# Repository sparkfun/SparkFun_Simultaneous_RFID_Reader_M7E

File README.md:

SparkFun Simultaneous RFID Reader - M7E Hecto
============================================

[

[*SparkFun Simultaneous RFID Reader - M7E Hecto*](https://www.sparkfun.com/products/24738)

The SparkFun Simultaneous RFID Reader - M7E Hecto features M7E-HECTO UHF RFID reader from JADAK<sup>&copy;</sup>. We loved the capabilities of the previous version of this RFID reader, the M6E, so we created this design featuring the M7E with an on-board USB-C connector and CH340C USB to UART converter to quickly connect the board to a computer and read tags with no soldering required.

Along with the USB-C connector, the Simultaneous RFID Reader 3.3V has a 0.1"-spaced PTH header for connecting it to an external converter or to a 3.3V microcontroller of your choice to use it with the SparkFun Simultaneous RFID Tag Reader Library. A 2-way switch on the board allows for easy switching between the included communication interfaces.

Repository Contents
-------------------

* **/Documents** - Datasheets, additional product information 
* **/Hardware** - Eagle design files (.brd, .sch)
* **/Production** - Production panel files (.brd)
* **/docs** - Documentation files for the SparkFun Simultaneous RFID Reader - M7E Hecto

Documentation
--------------
* **[Hookup Guide](https://sparkfun.github.io/SparkFun_Simultaneous_RFID_Reader_M7E)** - Basic hookup guide for the SparkFun Simultaneous RFID Reader - M7E Hecto.
* **[SparkFun Simultaneous RFID Tag Reader Library](https://github.com/sparkfun/SparkFun_Simultaneous_RFID_Tag_Reader_Library)** - Arduino library for SparkFun Simultaneous RFID Readers.

Product Versions
----------------
* [WRL-24738](https://www.sparkfun.com/products/24738) - Initial release

License Information
-------------------

This product is _**open source**_! 

Please review the LICENSE.md file for license information. 

If you have any questions or concerns on licensing, please contact technical support on our [SparkFun forums](https://forum.sparkfun.com/viewforum.php?f=152).

Distributed as-is; no warranty is given.

- Your friends at SparkFun.

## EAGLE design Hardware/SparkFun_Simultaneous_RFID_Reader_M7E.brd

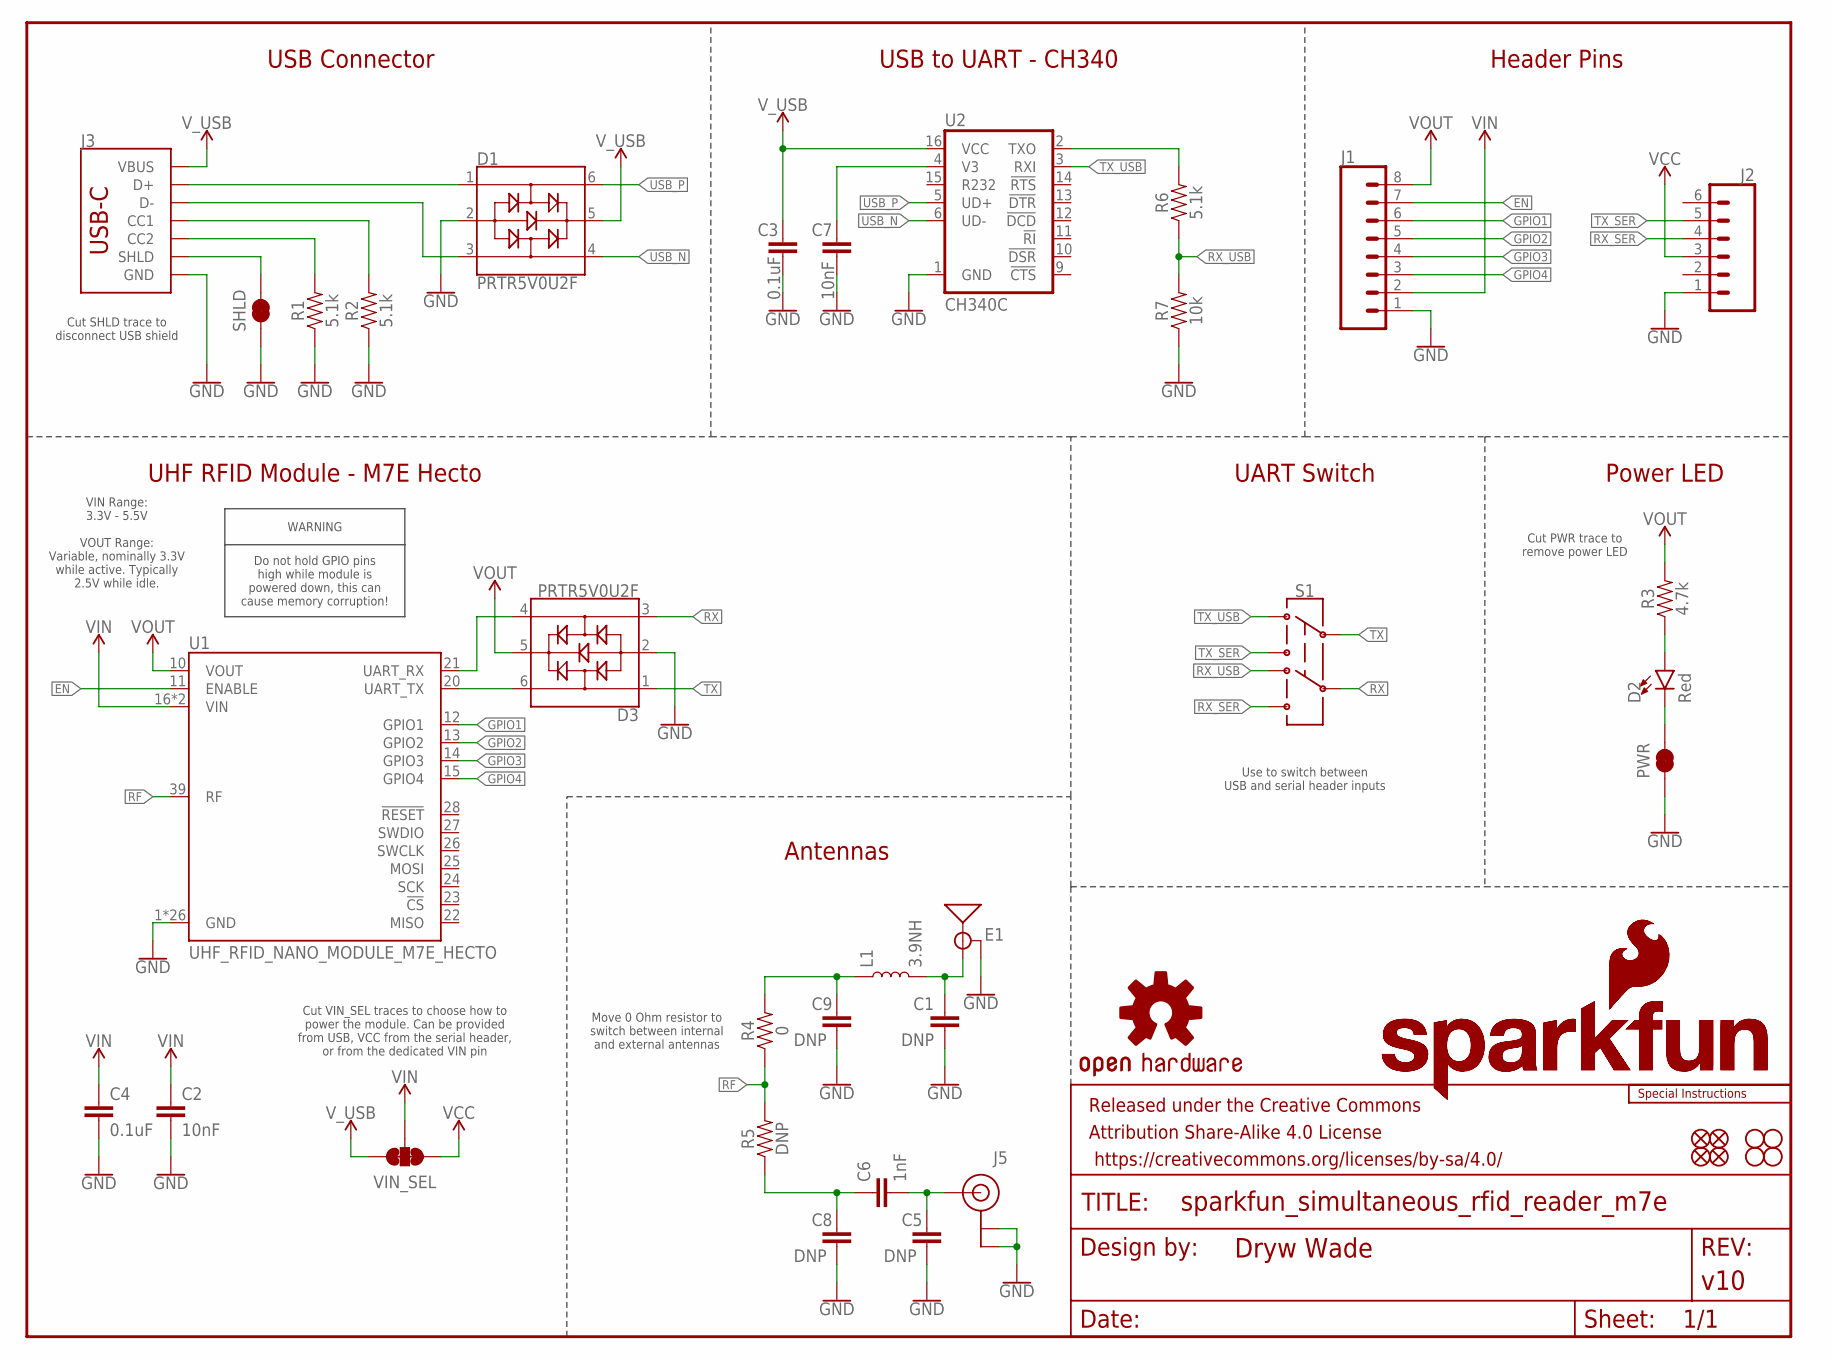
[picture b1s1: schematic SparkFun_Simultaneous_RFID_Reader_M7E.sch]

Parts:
C1, C5, C8, C9: DNP; 0603
C2, C7: 10nF; 0603
C3, C4: 0.1uF; 0603
C6: 1nF; 0603
D1, D3: PRTR5V0U2F; SOT886
D2: Red; LED-0603
E1: ANTENNA-GROUNDEDTRACE-915MHZ; TRACE_ANTENNA_915MHZ_THINGMAGIC
FD1, FD2, FD3, FD4: FIDUCIAL1X2; FIDUCIAL-1X2
FRAME1: FRAME-LETTER; CREATIVE_COMMONS
H1, H2, H3, H4: STAND-OFF
J1: CONN_08NO_SILK_DNP; 1X08_NO_SILK
J2: CONN_06NO_SILK_NO_POP; 1X06_NO_SILK
J3: USB_C_2-LAYER_PADS; USB-C-16P-2LAYER-PADS
J5: U.FL
L1: 3.9NH; 0603
LOGO1: OSHW-LOGOM; OSHW-LOGO-M
LOGO2, LOGO3: SFE_LOGO_NAME_FLAME.2_INCH; SFE_LOGO_NAME_FLAME_.2
LOGO4: SPECIAL_INSTRUCTIONS-ORDERING; ORDERING_INSTRUCTIONS
PWR: JUMPER-SMT_2_NC_TRACE_SILK; SMT-JUMPER_2_NC_TRACE_SILK
R1, R2, R6: 5.1k; 0603
R3: 4.7k; 0603
R4: 0; 0603
R5: DNP; 0603
R7: 10k; 0603
S1: SWITCH-DPDT-SMD-AYZ0202; SWITCH_DPDT_SMD_AYZ0202
SHLD: JUMPER-SMT_2_NC_TRACE_SILK; SMT-JUMPER_2_NC_TRACE_SILK
U1: UHF_RFID_NANO_MODULE_M7E_HECTO; M7E_HECTO_MODULE
U2: CH340C; SO016
VIN_SEL: JUMPER-SMT_3_2-NC_TRACE_SILK; SMT-JUMPER_3_2-NC_TRACE_SILK

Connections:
EN: J1.7, U1.11 (ENABLE)
GND: C1.2, C2.2, C3.2, C4.2, C5.2, C7.2, C8.2, C9.2, D1.2, D3.2, E1.GND@1 (GND), E1.GND@2 (GND), E1.GND@3 (GND), J1.1, J2.1, J3.GND, J3.GND2 (GND), J5.1 (GND), J5.2 (GND), PWR.1, R1.1, R2.1, R7.1, SHLD.1, U1.1 (GND), U1.2 (GND), U1.3 (GND), U1.4 (GND), U1.5 (GND), U1.6 (GND), U1.7 (GND), U1.8 (GND), U1.9 (GND), U1.18 (GND), U1.19 (GND), U1.29 (GND), U1.30 (GND), U1.31 (GND), U1.32 (GND), U1.33 (GND), U1.34 (GND), U1.35 (GND), U1.36 (GND), U1.37 (GND), U1.38 (GND), U1.40 (GND), U1.41 (GND), U1.GND_PAD1 (GND), U1.GND_PAD2 (GND), U1.GND_PAD3 (GND), U2.1 (GND)
GPIO1: J1.6, U1.12 (GPIO1)
GPIO2: J1.5, U1.13 (GPIO2)
GPIO3: J1.4, U1.14 (GPIO3)
GPIO4: J1.3, U1.15 (GPIO4)
unnamed: C1.1, E1.ANT (SIGNAL), L1.2
unnamed: D2.A, R3.1
unnamed: J3.B5 (CC2), R1.2
unnamed: J3.A5 (CC1), R2.2
unnamed: D1.1, J3.A6 (D+), J3.B6 (D+)
unnamed: D2.C, PWR.2
unnamed: D1.3, J3.A7 (D-), J3.B7 (D-)
unnamed: C6.1, C8.1, R5.1
unnamed: C5.1, C6.2, J5.FEED (SIGNAL)
unnamed: C9.1, L1.1, R4.2
unnamed: C7.1, U2.4 (V3)
unnamed: D3.6, U1.20 (UART_TX)
unnamed: D3.4, U1.21 (UART_RX)
unnamed: R6.2, U2.2 (TXO)
RF: R4.1, R5.2, U1.39 (RF)
RX: D3.3, S1.5
RX_SER: J2.4, S1.4
RX_USB: R6.1, R7.2, S1.6
SHLD: J3.SHLD1 (SHLD), J3.SHLD2 (SHLD), J3.SHLD3 (SHLD), J3.SHLD4 (SHLD), SHLD.2
TX: D3.1, S1.2
TX_SER: J2.5, S1.1
TX_USB: S1.3, U2.3 (RXI)
USB_N: D1.4, U2.6 (UD-)
USB_P: D1.6, U2.5 (UD+)
VCC: J2.3, VIN_SEL.1
VIN: C2.1, C4.1, J1.2, U1.16 (VIN), U1.17 (VIN), VIN_SEL.2
VOUT: D3.5, J1.8, R3.2, U1.10 (VOUT)
V_USB: C3.1, D1.5, J3.VBUS1 (VBUS), J3.VBUS2 (VBUS), U2.16 (VCC), VIN_SEL.3

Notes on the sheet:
WARNING
Do not hold GPIO pins high while module is powered down, this can cause memory corruption!
Cut VIN_SEL traces to choose how to power the module. Can be provided from USB, VCC from the serial header, or from the dedicated VIN pin
Cut SHLD trace to disconnect USB shield
USB Connector
USB to UART - CH340
Header Pins
Power LED
Antennas
UHF RFID Module - M7E Hecto
UART Switch
Move 0 Ohm resistor to switch between internal and external antennas
VOUT Range: Variable, nominally 3.3V while active. Typically 2.5V while idle.
Cut PWR trace to remove power LED
Use to switch between USB and serial header inputs
VIN Range: 3.3V - 5.5V

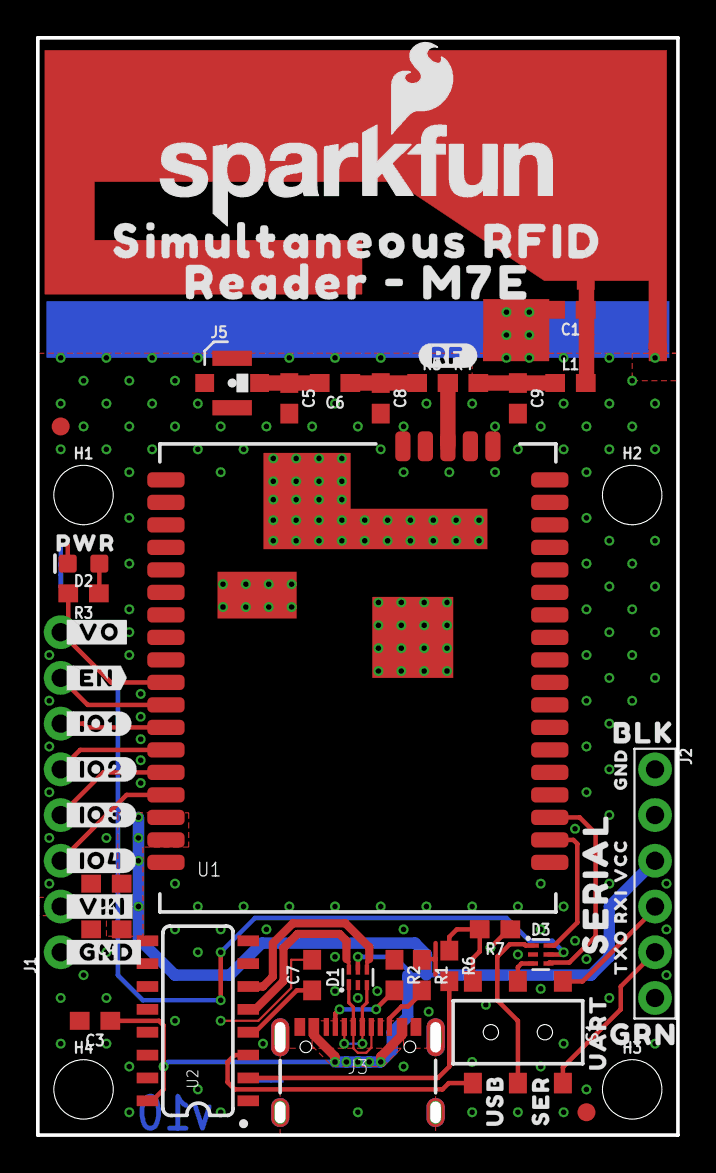
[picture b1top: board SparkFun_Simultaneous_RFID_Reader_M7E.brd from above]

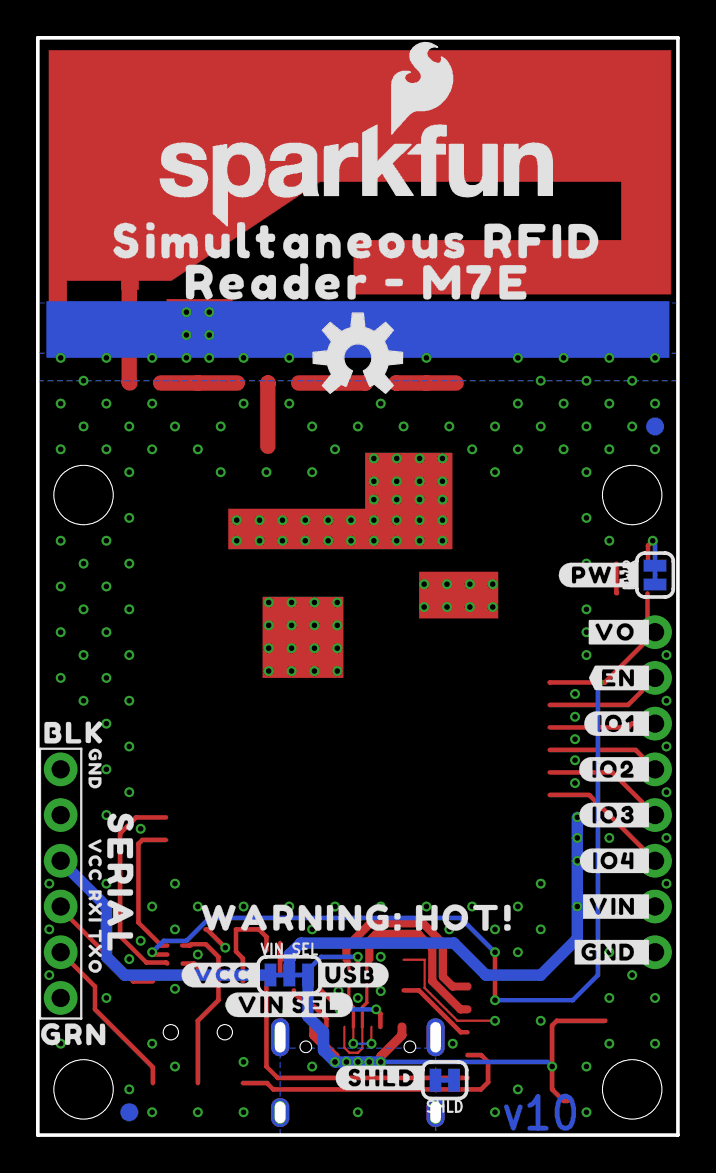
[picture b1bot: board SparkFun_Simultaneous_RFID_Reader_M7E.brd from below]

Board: 2 copper layers, 35.2 x 60.6 mm, 77 parts (24 on the bottom side), 34 nets.

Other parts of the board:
U$1, U$19: SIMULTANEOUS_RFID0
U$2, U$20: READER_#_M7E0
U$3: #USB#0
U$4: #VCC#0
U$5, U$7: SERIAL0
U$6: #_GND#0
U$8: UART0
U$10: #_VIN#0
U$11: #_IO4#0
U$12: #_IO3#0
U$13: #_IO2#0
U$14: #_IO1#0
U$15: #_EN#0
U$16: SER0
U$17: #VIN_SEL#0
U$18: #VO_#0
U$21: #_VO#0
U$27: #GND_#0
U$39: #EN_#0
U$40: #IO1_#0
U$41: #IO2_#0
U$42: #IO3_#0
U$43: #IO4_#0
U$44: #VIN_#0
U$45: USB0
U$49: #PWR#0
U$50: #SHLD#0
U$52: PWR0
U$56: #RF#0
U$57: WARNING#_HOT##0

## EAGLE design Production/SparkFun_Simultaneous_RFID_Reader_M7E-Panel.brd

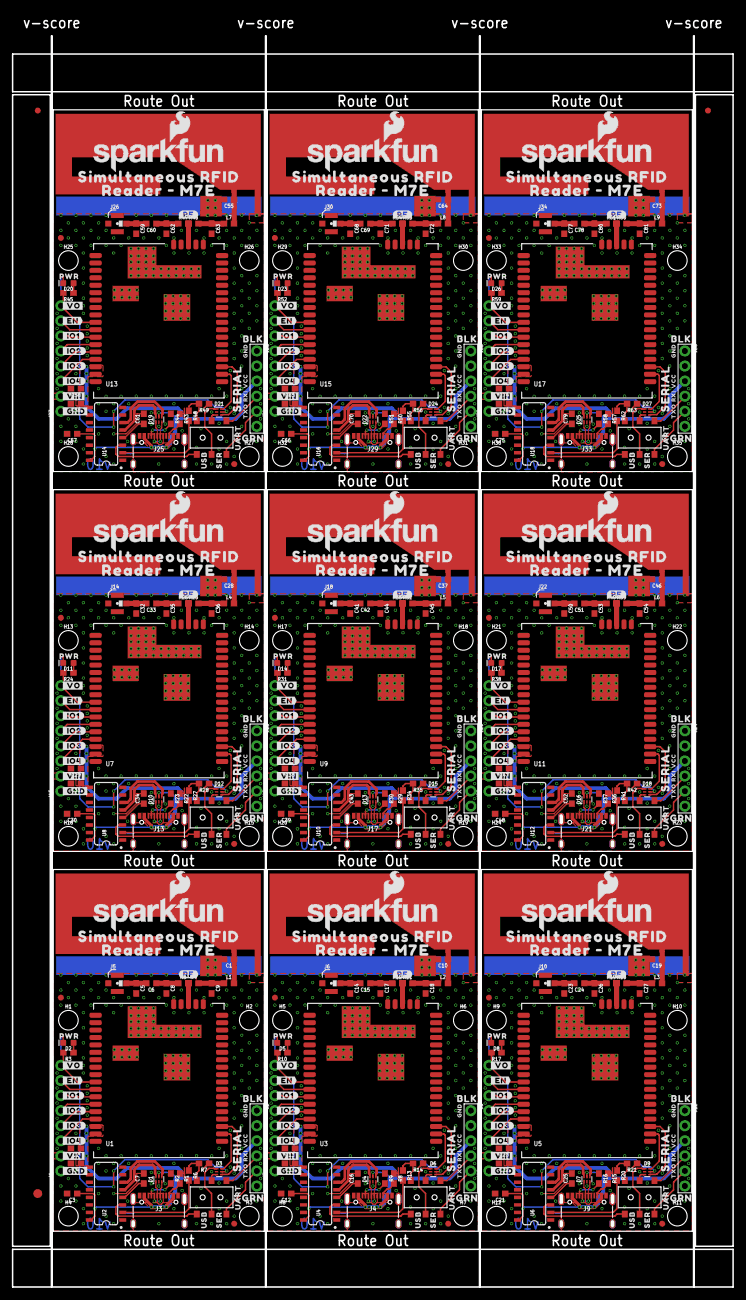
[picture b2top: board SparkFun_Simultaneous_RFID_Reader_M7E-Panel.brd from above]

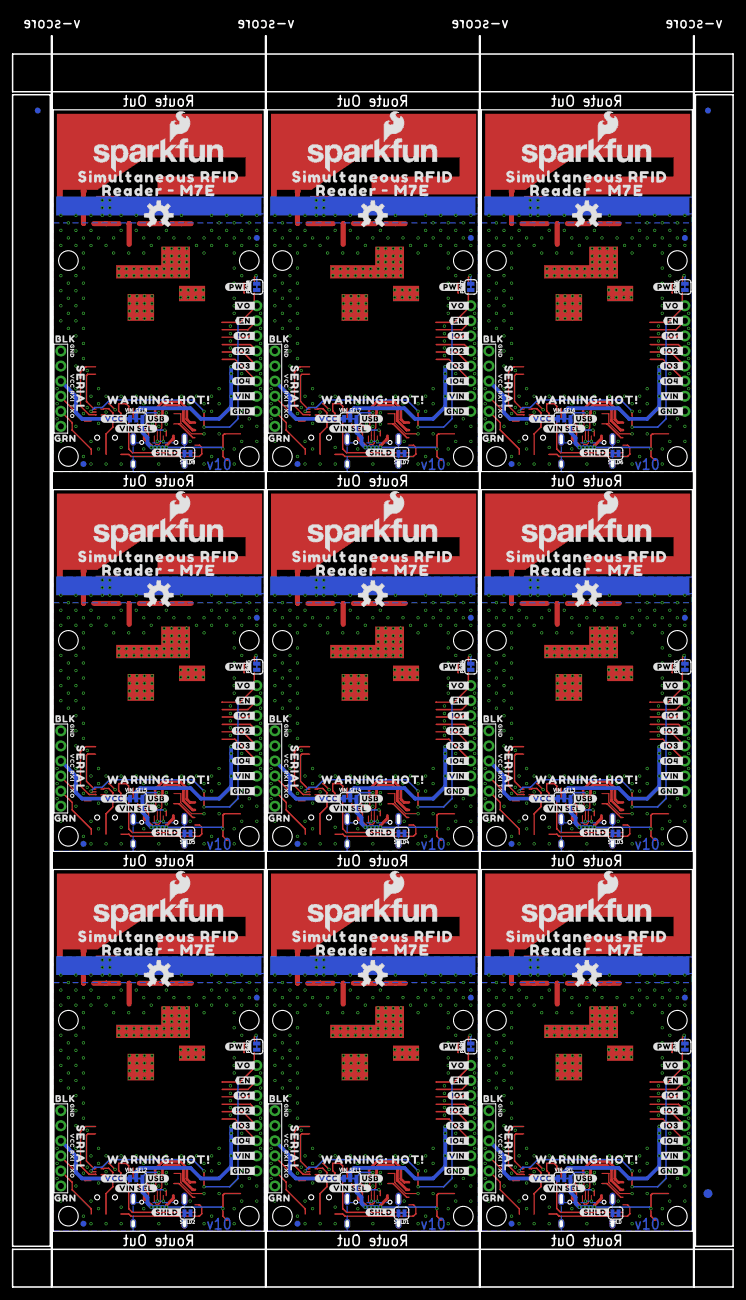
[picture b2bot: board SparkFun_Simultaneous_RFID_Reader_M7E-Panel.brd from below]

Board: 2 copper layers, 121.1 x 214.5 mm, 681 parts (219 on the bottom side), 306 nets.

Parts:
C1, C5, C8, C9, C10, C14, C17, C18, C19, C23, C26, C27, C28, C32, C35, C36, C37, C41, C44, C45, C46, C50, C53, C54, C55, C59, C62, C63, C64, C68, C71, C72, C73, C77, C80, C81: DNP; 0603
C2, C7, C11, C16, C20, C25, C29, C34, C38, C43, C47, C52, C56, C61, C65, C70, C74, C79: 10nF; 0603
C3, C4, C12, C13, C21, C22, C30, C31, C39, C40, C48, C49, C57, C58, C66, C67, C75, C76: 0.1uF; 0603
C6, C15, C24, C33, C42, C51, C60, C69, C78: 1nF; 0603
D1, D3, D4, D6, D7, D9, D10, D12, D13, D15, D16, D18, D19, D21, D22, D24, D25, D27: PRTR5V0U2F; SOT886
D2, D5, D8, D11, D14, D17, D20, D23, D26: Red; LED-0603
E1, E2, E3, E4, E5, E6, E7, E8, E9: ANTENNA-GROUNDEDTRACE-915MHZ; TRACE_ANTENNA_915MHZ_THINGMAGIC
E$1, E$2, E$3, E$4: FIDUCIAL-1X2
E$5, E$6: FIDUCIAL-1.5X3
FD1, FD2, FD3, FD4, FD5, FD6, FD7, FD8, FD9, FD10, FD11, FD12, FD13, FD14, FD15, FD16, FD17, FD18, FD19, FD20, FD21, FD22, FD23, FD24, FD25, FD26, FD27, FD28, FD29, FD30, FD31, FD32, FD33, FD34, FD35, FD36: FIDUCIAL1X2; FIDUCIAL-1X2
H1, H2, H3, H4, H5, H6, H7, H8, H9, H10, H11, H12, H13, H14, H15, H16, H17, H18, H19, H20, H21, H22, H23, H24, H25, H26, H27, H28, H29, H30, H31, H32, H33, H34, H35, H36: STAND-OFF
J1, J7, J11, J15, J19, J23, J27, J31, J35: 1X08_NO_SILK
J2, J8, J12, J16, J20, J24, J28, J32, J36: 1X06_NO_SILK
J3, J4, J9, J13, J17, J21, J25, J29, J33: USB-C-16P-2LAYER-PADS
J5, J6, J10, J14, J18, J22, J26, J30, J34: U.FL
L1, L2, L3, L4, L5, L6, L7, L8, L9: 3.9NH; 0603
LOGO1, LOGO4, LOGO7, LOGO10, LOGO13, LOGO16, LOGO19, LOGO22, LOGO25: OSHW-LOGOM; OSHW-LOGO-M
LOGO2, LOGO3, LOGO5, LOGO6, LOGO8, LOGO9, LOGO11, LOGO12, LOGO14, LOGO15, LOGO17, LOGO18, LOGO20, LOGO21, LOGO23, LOGO24, LOGO26, LOGO27: SFE_LOGO_NAME_FLAME.2_INCH; SFE_LOGO_NAME_FLAME_.2
PWR, PWR1, PWR2, PWR3, PWR4, PWR5, PWR6, PWR7, PWR8: JUMPER-SMT_2_NC_TRACE_SILK; SMT-JUMPER_2_NC_TRACE_SILK
R1, R2, R6, R8, R9, R13, R15, R16, R20, R22, R23, R27, R29, R30, R34, R36, R37, R41, R43, R44, R48, R50, R51, R55, R57, R58, R62: 5.1k; 0603
R3, R10, R17, R24, R31, R38, R45, R52, R59: 4.7k; 0603
R4, R11, R18, R25, R32, R39, R46, R53, R60: 0; 0603
R5, R12, R19, R26, R33, R40, R47, R54, R61: DNP; 0603
R7, R14, R21, R28, R35, R42, R49, R56, R63: 10k; 0603
S1, S2, S3, S4, S5, S6, S7, S8, S9: SWITCH_DPDT_SMD_AYZ0202
SHLD, SHLD1, SHLD2, SHLD3, SHLD4, SHLD5, SHLD6, SHLD7, SHLD8: JUMPER-SMT_2_NC_TRACE_SILK; SMT-JUMPER_2_NC_TRACE_SILK
U1, U3, U5, U7, U9, U11, U13, U15, U17: UHF_RFID_NANO_MODULE_M7E_HECTO; M7E_HECTO_MODULE
U2, U4, U6, U8, U10, U12, U14, U16, U18: CH340C; SO016
U$1, U$19, U$58, U$60, U$91, U$93, U$124, U$126, U$157, U$159, U$190, U$192, U$223, U$225, U$256, U$258, U$289, U$291: SIMULTANEOUS_RFID0
U$2, U$20, U$59, U$61, U$92, U$94, U$125, U$127, U$158, U$160, U$191, U$193, U$224, U$226, U$257, U$259, U$290, U$292: READER_#_M7E0
U$3, U$62, U$95, U$128, U$161, U$194, U$227, U$260, U$293: #USB#0
U$4, U$63, U$96, U$129, U$162, U$195, U$228, U$261, U$294: #VCC#0
U$5, U$7, U$51, U$53, U$87, U$88, U$120, U$121, U$153, U$154, U$186, U$187, U$219, U$220, U$252, U$253, U$285, U$286: SERIAL0
U$6, U$9, U$67, U$100, U$133, U$166, U$199, U$232, U$265: #_GND#0
U$8, U$54, U$89, U$122, U$155, U$188, U$221, U$254, U$287: UART0
U$10, U$22, U$68, U$101, U$134, U$167, U$200, U$233, U$266: #_VIN#0
U$11, U$23, U$69, U$102, U$135, U$168, U$201, U$234, U$267: #_IO4#0
U$12, U$24, U$70, U$103, U$136, U$169, U$202, U$235, U$268: #_IO3#0
U$13, U$25, U$71, U$104, U$137, U$170, U$203, U$236, U$269: #_IO2#0
U$14, U$26, U$72, U$105, U$138, U$171, U$204, U$237, U$270: #_IO1#0
U$15, U$28, U$73, U$106, U$139, U$172, U$205, U$238, U$271: #_EN#0
U$16, U$55, U$90, U$123, U$156, U$189, U$222, U$255, U$288: SER0
U$17, U$64, U$97, U$130, U$163, U$196, U$229, U$262, U$295: #VIN_SEL#0
U$18, U$66, U$99, U$132, U$165, U$198, U$231, U$264, U$297: #VO_#0
U$21, U$65, U$98, U$131, U$164, U$197, U$230, U$263, U$296: #_VO#0
U$27, U$29, U$74, U$107, U$140, U$173, U$206, U$239, U$272: #GND_#0
U$30, U$39, U$75, U$108, U$141, U$174, U$207, U$240, U$273: #EN_#0
U$31, U$40, U$76, U$109, U$142, U$175, U$208, U$241, U$274: #IO1_#0
U$32, U$41, U$77, U$110, U$143, U$176, U$209, U$242, U$275: #IO2_#0
U$33, U$42, U$78, U$111, U$144, U$177, U$210, U$243, U$276: #IO3_#0
U$34, U$43, U$79, U$112, U$145, U$178, U$211, U$244, U$277: #IO4_#0
U$35, U$44, U$80, U$113, U$146, U$179, U$212, U$245, U$278: #VIN_#0
U$36, U$45, U$81, U$114, U$147, U$180, U$213, U$246, U$279: USB0
U$37, U$49, U$82, U$115, U$148, U$181, U$214, U$247, U$280: #PWR#0
U$38, U$50, U$83, U$116, U$149, U$182, U$215, U$248, U$281: #SHLD#0
U$46, U$52, U$84, U$117, U$150, U$183, U$216, U$249, U$282: PWR0
U$47, U$56, U$85, U$118, U$151, U$184, U$217, U$250, U$283: #RF#0
U$48, U$57, U$86, U$119, U$152, U$185, U$218, U$251, U$284: WARNING#_HOT##0
VIN_SEL, VIN_SEL1, VIN_SEL2, VIN_SEL3, VIN_SEL4, VIN_SEL5, VIN_SEL6, VIN_SEL7, VIN_SEL8: JUMPER-SMT_3_2-NC_TRACE_SILK; SMT-JUMPER_3_2-NC_TRACE_SILK

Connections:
EN: J1.7, U1.11
EN1: J7.7, U3.11
EN2: J11.7, U5.11
EN3: J15.7, U7.11
EN4: J19.7, U9.11
EN5: J23.7, U11.11
EN6: J27.7, U13.11
EN7: J31.7, U15.11
EN8: J35.7, U17.11
GND: C1.2, C2.2, C3.2, C4.2, C5.2, C7.2, C8.2, C9.2, D1.2, D3.2, E1.GND@1, E1.GND@2, E1.GND@3, J1.1, J2.1, J3.GND, J3.GND2, J5.1, J5.2, PWR.1, R1.1, R2.1, R7.1, SHLD.1, U1.1, U1.2, U1.3, U1.4, U1.5, U1.6, U1.7, U1.8, U1.9, U1.18, U1.19, U1.29, U1.30, U1.31, U1.32, U1.33, U1.34, U1.35, U1.36, U1.37, U1.38, U1.40, U1.41, U1.GND_PAD1, U1.GND_PAD2, U1.GND_PAD3, U2.1
GND1: C10.2, C11.2, C12.2, C13.2, C14.2, C16.2, C17.2, C18.2, D4.2, D6.2, E2.GND@1, E2.GND@2, E2.GND@3, J4.GND, J4.GND2, J6.1, J6.2, J7.1, J8.1, PWR1.1, R8.1, R9.1, R14.1, SHLD1.1, U3.1, U3.2, U3.3, U3.4, U3.5, U3.6, U3.7, U3.8, U3.9, U3.18, U3.19, U3.29, U3.30, U3.31, U3.32, U3.33, U3.34, U3.35, U3.36, U3.37, U3.38, U3.40, U3.41, U3.GND_PAD1, U3.GND_PAD2, U3.GND_PAD3, U4.1
GND2: C19.2, C20.2, C21.2, C22.2, C23.2, C25.2, C26.2, C27.2, D7.2, D9.2, E3.GND@1, E3.GND@2, E3.GND@3, J9.GND, J9.GND2, J10.1, J10.2, J11.1, J12.1, PWR2.1, R15.1, R16.1, R21.1, SHLD2.1, U5.1, U5.2, U5.3, U5.4, U5.5, U5.6, U5.7, U5.8, U5.9, U5.18, U5.19, U5.29, U5.30, U5.31, U5.32, U5.33, U5.34, U5.35, U5.36, U5.37, U5.38, U5.40, U5.41, U5.GND_PAD1, U5.GND_PAD2, U5.GND_PAD3, U6.1
GND3: C28.2, C29.2, C30.2, C31.2, C32.2, C34.2, C35.2, C36.2, D10.2, D12.2, E4.GND@1, E4.GND@2, E4.GND@3, J13.GND, J13.GND2, J14.1, J14.2, J15.1, J16.1, PWR3.1, R22.1, R23.1, R28.1, SHLD3.1, U7.1, U7.2, U7.3, U7.4, U7.5, U7.6, U7.7, U7.8, U7.9, U7.18, U7.19, U7.29, U7.30, U7.31, U7.32, U7.33, U7.34, U7.35, U7.36, U7.37, U7.38, U7.40, U7.41, U7.GND_PAD1, U7.GND_PAD2, U7.GND_PAD3, U8.1
GND4: C37.2, C38.2, C39.2, C40.2, C41.2, C43.2, C44.2, C45.2, D13.2, D15.2, E5.GND@1, E5.GND@2, E5.GND@3, J17.GND, J17.GND2, J18.1, J18.2, J19.1, J20.1, PWR4.1, R29.1, R30.1, R35.1, SHLD4.1, U9.1, U9.2, U9.3, U9.4, U9.5, U9.6, U9.7, U9.8, U9.9, U9.18, U9.19, U9.29, U9.30, U9.31, U9.32, U9.33, U9.34, U9.35, U9.36, U9.37, U9.38, U9.40, U9.41, U9.GND_PAD1, U9.GND_PAD2, U9.GND_PAD3, U10.1
GND5: C46.2, C47.2, C48.2, C49.2, C50.2, C52.2, C53.2, C54.2, D16.2, D18.2, E6.GND@1, E6.GND@2, E6.GND@3, J21.GND, J21.GND2, J22.1, J22.2, J23.1, J24.1, PWR5.1, R36.1, R37.1, R42.1, SHLD5.1, U11.1, U11.2, U11.3, U11.4, U11.5, U11.6, U11.7, U11.8, U11.9, U11.18, U11.19, U11.29, U11.30, U11.31, U11.32, U11.33, U11.34, U11.35, U11.36, U11.37, U11.38, U11.40, U11.41, U11.GND_PAD1, U11.GND_PAD2, U11.GND_PAD3, U12.1
GND6: C55.2, C56.2, C57.2, C58.2, C59.2, C61.2, C62.2, C63.2, D19.2, D21.2, E7.GND@1, E7.GND@2, E7.GND@3, J25.GND, J25.GND2, J26.1, J26.2, J27.1, J28.1, PWR6.1, R43.1, R44.1, R49.1, SHLD6.1, U13.1, U13.2, U13.3, U13.4, U13.5, U13.6, U13.7, U13.8, U13.9, U13.18, U13.19, U13.29, U13.30, U13.31, U13.32, U13.33, U13.34, U13.35, U13.36, U13.37, U13.38, U13.40, U13.41, U13.GND_PAD1, U13.GND_PAD2, U13.GND_PAD3, U14.1
GND7: C64.2, C65.2, C66.2, C67.2, C68.2, C70.2, C71.2, C72.2, D22.2, D24.2, E8.GND@1, E8.GND@2, E8.GND@3, J29.GND, J29.GND2, J30.1, J30.2, J31.1, J32.1, PWR7.1, R50.1, R51.1, R56.1, SHLD7.1, U15.1, U15.2, U15.3, U15.4, U15.5, U15.6, U15.7, U15.8, U15.9, U15.18, U15.19, U15.29, U15.30, U15.31, U15.32, U15.33, U15.34, U15.35, U15.36, U15.37, U15.38, U15.40, U15.41, U15.GND_PAD1, U15.GND_PAD2, U15.GND_PAD3, U16.1
GND8: C73.2, C74.2, C75.2, C76.2, C77.2, C79.2, C80.2, C81.2, D25.2, D27.2, E9.GND@1, E9.GND@2, E9.GND@3, J33.GND, J33.GND2, J34.1, J34.2, J35.1, J36.1, PWR8.1, R57.1, R58.1, R63.1, SHLD8.1, U17.1, U17.2, U17.3, U17.4, U17.5, U17.6, U17.7, U17.8, U17.9, U17.18, U17.19, U17.29, U17.30, U17.31, U17.32, U17.33, U17.34, U17.35, U17.36, U17.37, U17.38, U17.40, U17.41, U17.GND_PAD1, U17.GND_PAD2, U17.GND_PAD3, U18.1
GPIO1: J1.6, U1.12
GPIO2: J1.5, U1.13
GPIO3: J1.4, U1.14
GPIO4: J1.3, U1.15
GPIO5: J7.6, U3.12
GPIO6: J7.5, U3.13
GPIO7: J7.4, U3.14
GPIO8: J7.3, U3.15
GPIO9: J11.6, U5.12
GPIO10: J11.5, U5.13
GPIO11: J11.4, U5.14
GPIO12: J11.3, U5.15
GPIO13: J15.6, U7.12
GPIO14: J15.5, U7.13
GPIO15: J15.4, U7.14
GPIO16: J15.3, U7.15
GPIO17: J19.6, U9.12
GPIO18: J19.5, U9.13
GPIO19: J19.4, U9.14
GPIO20: J19.3, U9.15
GPIO21: J23.6, U11.12
GPIO22: J23.5, U11.13
GPIO23: J23.4, U11.14
GPIO24: J23.3, U11.15
GPIO25: J27.6, U13.12
GPIO26: J27.5, U13.13
GPIO27: J27.4, U13.14
GPIO28: J27.3, U13.15
GPIO29: J31.6, U15.12
GPIO30: J31.5, U15.13
GPIO31: J31.4, U15.14
GPIO32: J31.3, U15.15
GPIO33: J35.6, U17.12
GPIO34: J35.5, U17.13
GPIO35: J35.4, U17.14
GPIO36: J35.3, U17.15
unnamed: C1.1, E1.ANT, L1.2
unnamed: D2.A, R3.1
unnamed: J3.B5, R1.2
unnamed: J3.A5, R2.2
unnamed: D1.1, J3.A6, J3.B6
unnamed: D2.C, PWR.2
unnamed: D1.3, J3.A7, J3.B7
unnamed: C6.1, C8.1, R5.1
unnamed: C5.1, C6.2, J5.FEED
unnamed: C9.1, L1.1, R4.2
unnamed: C7.1, U2.4
unnamed: D3.6, U1.20
unnamed: D3.4, U1.21
unnamed: R6.2, U2.2
unnamed: C10.1, E2.ANT, L2.2
unnamed: J4.B5, R8.2
unnamed: J4.A5, R9.2
unnamed: D4.1, J4.A6, J4.B6
unnamed: D4.3, J4.A7, J4.B7
unnamed: C15.1, C17.1, R12.1
unnamed: C14.1, C15.2, J6.FEED
unnamed: C18.1, L2.1, R11.2
unnamed: C16.1, U4.4
unnamed: D6.6, U3.20
unnamed: D6.4, U3.21
unnamed: D5.A, R10.1
unnamed: D5.C, PWR1.2
unnamed: R13.2, U4.2
unnamed: C19.1, E3.ANT, L3.2
unnamed: J9.B5, R15.2
unnamed: J9.A5, R16.2
unnamed: D7.1, J9.A6, J9.B6
unnamed: D7.3, J9.A7, J9.B7
unnamed: C24.1, C26.1, R19.1
unnamed: C23.1, C24.2, J10.FEED
unnamed: C27.1, L3.1, R18.2
unnamed: C25.1, U6.4
unnamed: D9.6, U5.20
unnamed: D9.4, U5.21
unnamed: D8.A, R17.1
unnamed: D8.C, PWR2.2
unnamed: R20.2, U6.2
unnamed: C28.1, E4.ANT, L4.2
unnamed: J13.B5, R22.2
unnamed: J13.A5, R23.2
unnamed: D10.1, J13.A6, J13.B6
unnamed: D10.3, J13.A7, J13.B7
unnamed: C33.1, C35.1, R26.1
unnamed: C32.1, C33.2, J14.FEED
unnamed: C36.1, L4.1, R25.2
unnamed: C34.1, U8.4
unnamed: D12.6, U7.20
unnamed: D12.4, U7.21
unnamed: D11.A, R24.1
unnamed: D11.C, PWR3.2
unnamed: R27.2, U8.2
unnamed: C37.1, E5.ANT, L5.2
unnamed: J17.B5, R29.2
unnamed: J17.A5, R30.2
unnamed: D13.1, J17.A6, J17.B6
unnamed: D13.3, J17.A7, J17.B7
unnamed: C42.1, C44.1, R33.1
unnamed: C41.1, C42.2, J18.FEED
unnamed: C45.1, L5.1, R32.2
unnamed: C43.1, U10.4
unnamed: D15.6, U9.20
unnamed: D15.4, U9.21
unnamed: D14.A, R31.1
unnamed: D14.C, PWR4.2
unnamed: R34.2, U10.2
unnamed: C46.1, E6.ANT, L6.2
unnamed: J21.B5, R36.2
unnamed: J21.A5, R37.2
unnamed: D16.1, J21.A6, J21.B6
unnamed: D16.3, J21.A7, J21.B7
unnamed: C51.1, C53.1, R40.1
unnamed: C50.1, C51.2, J22.FEED
unnamed: C54.1, L6.1, R39.2
unnamed: C52.1, U12.4
unnamed: D18.6, U11.20
unnamed: D18.4, U11.21
unnamed: D17.A, R38.1
unnamed: D17.C, PWR5.2
unnamed: R41.2, U12.2
unnamed: C55.1, E7.ANT, L7.2
unnamed: J25.B5, R43.2
unnamed: J25.A5, R44.2
unnamed: D19.1, J25.A6, J25.B6
unnamed: D19.3, J25.A7, J25.B7
unnamed: C60.1, C62.1, R47.1
unnamed: C59.1, C60.2, J26.FEED
unnamed: C63.1, L7.1, R46.2
unnamed: C61.1, U14.4
unnamed: D21.6, U13.20
unnamed: D21.4, U13.21
unnamed: D20.A, R45.1
unnamed: D20.C, PWR6.2
unnamed: R48.2, U14.2
unnamed: C64.1, E8.ANT, L8.2
unnamed: J29.B5, R50.2
unnamed: J29.A5, R51.2
unnamed: D22.1, J29.A6, J29.B6
unnamed: D22.3, J29.A7, J29.B7
unnamed: C69.1, C71.1, R54.1
unnamed: C68.1, C69.2, J30.FEED
unnamed: C72.1, L8.1, R53.2
unnamed: C70.1, U16.4
unnamed: D24.6, U15.20
unnamed: D24.4, U15.21
unnamed: D23.A, R52.1
unnamed: D23.C, PWR7.2
unnamed: R55.2, U16.2
unnamed: C73.1, E9.ANT, L9.2
unnamed: J33.B5, R57.2
unnamed: J33.A5, R58.2
unnamed: D25.1, J33.A6, J33.B6
unnamed: D25.3, J33.A7, J33.B7
unnamed: C78.1, C80.1, R61.1
unnamed: C77.1, C78.2, J34.FEED
unnamed: C81.1, L9.1, R60.2
unnamed: C79.1, U18.4
unnamed: D27.6, U17.20
unnamed: D27.4, U17.21
unnamed: D26.A, R59.1
unnamed: D26.C, PWR8.2
unnamed: R62.2, U18.2
RF: R4.1, R5.2, U1.39
RF1: R11.1, R12.2, U3.39
RF2: R18.1, R19.2, U5.39
RF3: R25.1, R26.2, U7.39
RF4: R32.1, R33.2, U9.39
RF5: R39.1, R40.2, U11.39
RF6: R46.1, R47.2, U13.39
RF7: R53.1, R54.2, U15.39
RF8: R60.1, R61.2, U17.39
RX: D3.3, S1.5
RX1: D6.3, S2.5
RX2: D9.3, S3.5
RX3: D12.3, S4.5
RX4: D15.3, S5.5
RX5: D18.3, S6.5
RX6: D21.3, S7.5
RX7: D24.3, S8.5
RX8: D27.3, S9.5
RX_SER: J2.4, S1.4
RX_SER1: J8.4, S2.4
RX_SER2: J12.4, S3.4
RX_SER3: J16.4, S4.4
RX_SER4: J20.4, S5.4
RX_SER5: J24.4, S6.4
RX_SER6: J28.4, S7.4
RX_SER7: J32.4, S8.4
RX_SER8: J36.4, S9.4
RX_USB: R6.1, R7.2, S1.6
RX_USB1: R13.1, R14.2, S2.6
RX_USB2: R20.1, R21.2, S3.6
RX_USB3: R27.1, R28.2, S4.6
RX_USB4: R34.1, R35.2, S5.6
RX_USB5: R41.1, R42.2, S6.6
RX_USB6: R48.1, R49.2, S7.6
RX_USB7: R55.1, R56.2, S8.6
RX_USB8: R62.1, R63.2, S9.6
SHLD: J3.SHLD1, J3.SHLD2, J3.SHLD3, J3.SHLD4, SHLD.2
SHLD1: J4.SHLD1, J4.SHLD2, J4.SHLD3, J4.SHLD4, SHLD1.2
SHLD2: J9.SHLD1, J9.SHLD2, J9.SHLD3, J9.SHLD4, SHLD2.2
SHLD3: J13.SHLD1, J13.SHLD2, J13.SHLD3, J13.SHLD4, SHLD3.2
SHLD4: J17.SHLD1, J17.SHLD2, J17.SHLD3, J17.SHLD4, SHLD4.2
SHLD5: J21.SHLD1, J21.SHLD2, J21.SHLD3, J21.SHLD4, SHLD5.2
SHLD6: J25.SHLD1, J25.SHLD2, J25.SHLD3, J25.SHLD4, SHLD6.2
SHLD7: J29.SHLD1, J29.SHLD2, J29.SHLD3, J29.SHLD4, SHLD7.2
SHLD8: J33.SHLD1, J33.SHLD2, J33.SHLD3, J33.SHLD4, SHLD8.2
TX: D3.1, S1.2
TX1: D6.1, S2.2
TX2: D9.1, S3.2
TX3: D12.1, S4.2
TX4: D15.1, S5.2
TX5: D18.1, S6.2
TX6: D21.1, S7.2
TX7: D24.1, S8.2
TX8: D27.1, S9.2
TX_SER: J2.5, S1.1
TX_SER1: J8.5, S2.1
TX_SER2: J12.5, S3.1
TX_SER3: J16.5, S4.1
TX_SER4: J20.5, S5.1
TX_SER5: J24.5, S6.1
TX_SER6: J28.5, S7.1
TX_SER7: J32.5, S8.1
TX_SER8: J36.5, S9.1
TX_USB: S1.3, U2.3
TX_USB1: S2.3, U4.3
TX_USB2: S3.3, U6.3
TX_USB3: S4.3, U8.3
TX_USB4: S5.3, U10.3
TX_USB5: S6.3, U12.3
TX_USB6: S7.3, U14.3
TX_USB7: S8.3, U16.3
TX_USB8: S9.3, U18.3
USB_N: D1.4, U2.6
USB_N1: D4.4, U4.6
USB_N2: D7.4, U6.6
USB_N3: D10.4, U8.6
USB_N4: D13.4, U10.6
USB_N5: D16.4, U12.6
USB_N6: D19.4, U14.6
USB_N7: D22.4, U16.6
USB_N8: D25.4, U18.6
USB_P: D1.6, U2.5
USB_P1: D4.6, U4.5
USB_P2: D7.6, U6.5
USB_P3: D10.6, U8.5
USB_P4: D13.6, U10.5
USB_P5: D16.6, U12.5
USB_P6: D19.6, U14.5
USB_P7: D22.6, U16.5
USB_P8: D25.6, U18.5
VCC: J2.3, VIN_SEL.1
VCC1: J8.3, VIN_SEL1.1
VCC2: J12.3, VIN_SEL2.1
VCC3: J16.3, VIN_SEL3.1
VCC4: J20.3, VIN_SEL4.1
VCC5: J24.3, VIN_SEL5.1
VCC6: J28.3, VIN_SEL6.1
VCC7: J32.3, VIN_SEL7.1
VCC8: J36.3, VIN_SEL8.1
VIN: C2.1, C4.1, J1.2, U1.16, U1.17, VIN_SEL.2
VIN1: C11.1, C13.1, J7.2, U3.16, U3.17, VIN_SEL1.2
VIN2: C20.1, C22.1, J11.2, U5.16, U5.17, VIN_SEL2.2
VIN3: C29.1, C31.1, J15.2, U7.16, U7.17, VIN_SEL3.2
VIN4: C38.1, C40.1, J19.2, U9.16, U9.17, VIN_SEL4.2
VIN5: C47.1, C49.1, J23.2, U11.16, U11.17, VIN_SEL5.2
VIN6: C56.1, C58.1, J27.2, U13.16, U13.17, VIN_SEL6.2
VIN7: C65.1, C67.1, J31.2, U15.16, U15.17, VIN_SEL7.2
VIN8: C74.1, C76.1, J35.2, U17.16, U17.17, VIN_SEL8.2
VOUT: D3.5, J1.8, R3.2, U1.10
VOUT1: D6.5, J7.8, R10.2, U3.10
VOUT2: D9.5, J11.8, R17.2, U5.10
VOUT3: D12.5, J15.8, R24.2, U7.10
VOUT4: D15.5, J19.8, R31.2, U9.10
VOUT5: D18.5, J23.8, R38.2, U11.10
VOUT6: D21.5, J27.8, R45.2, U13.10
VOUT7: D24.5, J31.8, R52.2, U15.10
VOUT8: D27.5, J35.8, R59.2, U17.10
V_USB: C3.1, D1.5, J3.VBUS1, J3.VBUS2, U2.16, VIN_SEL.3
V_USB1: C12.1, D4.5, J4.VBUS1, J4.VBUS2, U4.16, VIN_SEL1.3
V_USB2: C21.1, D7.5, J9.VBUS1, J9.VBUS2, U6.16, VIN_SEL2.3
V_USB3: C30.1, D10.5, J13.VBUS1, J13.VBUS2, U8.16, VIN_SEL3.3
V_USB4: C39.1, D13.5, J17.VBUS1, J17.VBUS2, U10.16, VIN_SEL4.3
V_USB5: C48.1, D16.5, J21.VBUS1, J21.VBUS2, U12.16, VIN_SEL5.3
V_USB6: C57.1, D19.5, J25.VBUS1, J25.VBUS2, U14.16, VIN_SEL6.3
V_USB7: C66.1, D22.5, J29.VBUS1, J29.VBUS2, U16.16, VIN_SEL7.3
V_USB8: C75.1, D25.5, J33.VBUS1, J33.VBUS2, U18.16, VIN_SEL8.3

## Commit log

2024-01-02 Initial design with M7E
2024-01-02 Change VIN selection jumper
    Now uses a 3-way jumper to independently select USB, VCC from serial head, or just dedicated VIN pin
2024-01-02 Add user guide
2024-01-02 Change 3.3V net to VOUT
    The M7E internal regulator actually outputs 2.5V when idle
2024-01-03 Fix CH340 power
    Can't be powered by VOUT, because the module outputs 2.5V while idle, which is too low for the CH340
    Now powered by VUSB. The only problem here is that the output voltage is based on VCC, so a voltage divider is used to make the output voltage ~3.3V
2024-01-03 Add PROD_ID of M7E
2024-01-04 Design review updates
    Add polygons to better fan out USB traces from ESD diode pads
    Nudge R3 away from VOUT pad
    Add VOUT range to schematic
    Swap power LED and resistor for new version
    Move via out of VO silk label
    Nudge USB traces to get better GND pour around C7
2024-01-04 Design review update
    Actually update the power LED and resistor this time
    Actually move the via on the VO silk this time
    Actually nudge USB traces to get better GND pour around C7 this time
2024-01-05 Design review updates
    Update section titles in schematic
    Remote DTR and CTS silk from serial header
    Add ordering instructions
    Update measures
2024-01-05 Fix VO silk label
2024-01-05 Add v10 panel files
2024-01-11 Initial Docs commit
    Initial docs content commit.
2024-03-28 Fix DNP components and PROD_ID values
2024-04-04 Docs Photos update
    Initial photos commit.
2024-04-09 Docs photos update
    Adding revised overview photos, new assembly photos, and minor updates to hardware overview, assembly, and reader assistant sections.
2024-04-16 Docs update
    Adding back photos & updates to docs pages. Prepping for review & build.
2024-04-18 Docs Update
    Docs update in prep for final review.
2024-04-18 Update README.md
    Filling out README.md
2024-04-25 Docs Review
    Minor changes from docs review.
2024-05-02 Docs update
    Single page fix. Initial test for page publish fix.
2024-05-09 Update examples.md
    Adding in code snippets for updated examples on release.
2024-05-16 Docs Update
    Adding product showcase embed and minor edits to assembly & troubleshooting.
2024-05-16 Deployed 750e484 with MkDocs version: 1.6.0
2024-10-25 Update mkdocs.yml
    Analytics update
2024-10-25 Deployed 5d31a6f with MkDocs version: 1.6.1
2024-11-04 Update introduction.md
    Replacing RFID tag product details.
2024-11-04 Deployed b17afd9 with MkDocs version: 1.6.1
2024-11-04 Update introduction.md
    Updating incorrect links.

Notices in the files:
parts and their libraries:
SparkFun-Aesthetics: Licensing: Creative Commons ShareAlike 4.0 International - https://creativecommons.org/licenses/by-sa/4.0
SparkFun-Aesthetics: Released under the Creative Commons Attribution Share-Alike 4.0 License
SparkFun-Aesthetics: https://creativecommons.org/licenses/by-sa/4.0
